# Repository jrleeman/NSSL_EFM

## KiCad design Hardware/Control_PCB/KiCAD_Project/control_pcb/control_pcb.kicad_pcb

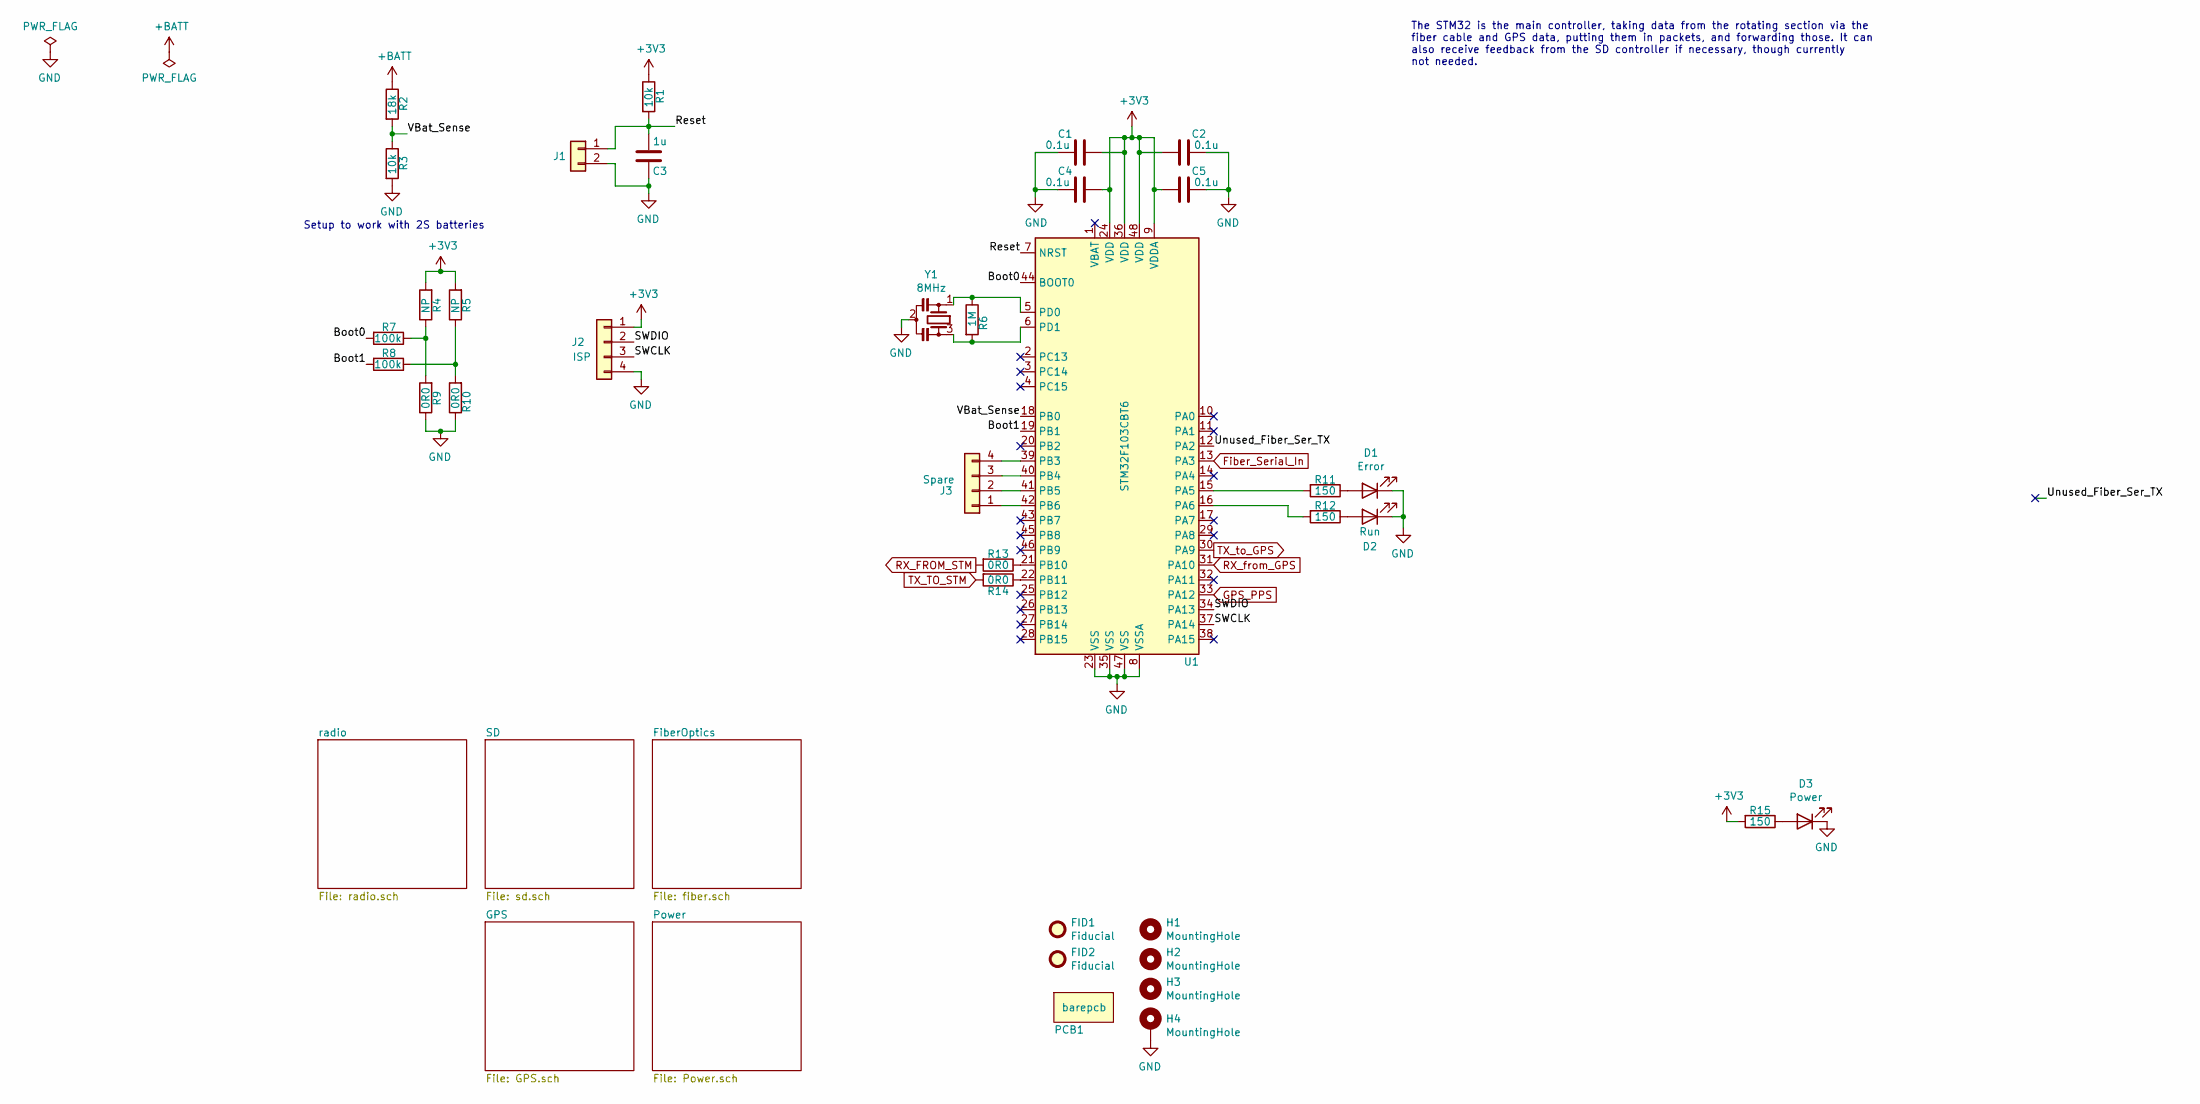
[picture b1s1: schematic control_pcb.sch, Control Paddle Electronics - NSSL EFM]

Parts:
C1, C2, C4, C5: 0.1u; C_0603_1608Metric
C3: 1u; C_0603_1608Metric
D1: Error; LED_0805_2012Metric
D2: Run; LED_0805_2012Metric
D3: Power; LED_0805_2012Metric
FID1, FID2: Fiducial; Fiducial_1mm_Mask2mm
H1, H2, H3: MountingHole; MountingHole_3.2mm_M3_ISO7380
H4: MountingHole; MountingHole_3.2mm_M3_ISO7380_Pad
J1: Conn_01x02; Pin_Header_Straight_1x02_Pitch2.54mm
J2: ISP; Pin_Header_Straight_1x04_Pitch2.54mm
J3: Spare; Pin_Header_Straight_1x04_Pitch2.54mm
PCB1: barepcb
R1, R3: 10k; R_0603_1608Metric
R2: 18k; R_0603_1608Metric
R4, R5: NP; R_0603_1608Metric
R6: 1M; R_0603_1608Metric
R7, R8: 100k; R_0603_1608Metric
R9, R10: 0R0; R_0603_1608Metric
R11, R12, R15: 150; R_0603_1608Metric
R13, R14: 1-0000006
U1: STM32F103CBT6; LQFP-48_7x7mm_Pitch0.5mm
Y1: 8MHz; Resonator

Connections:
+3V3: C1.2, C2.2, C4.2, C5.2, J2.1, R1.1, R4.2, R5.2, R15.2, U1.9 (VDDA), U1.24 (VDD), U1.36 (VDD), U1.48 (VDD); also elsewhere on the board
+BATT: R2.1; also elsewhere on the board
/Boot0: R7.2, U1.44 (BOOT0)
/Boot1: R8.2, U1.19 (PB1)
/Reset: C3.1, J1.1, R1.2, U1.7 (NRST)
/SWCLK: J2.3, U1.37 (PA14)
/SWDIO: J2.2, U1.34 (PA13)
/VBat_Sense: R2.2, R3.1, U1.18 (PB0)
Fiber_Serial_In: U1.13 (PA3); also elsewhere on the board
GND: C1.1, C2.1, C3.2, C4.1, C5.1, D1.1 (K), D2.1 (K), D3.1 (K), H4.1, J1.2, J2.4, R3.2, R9.1, R10.1, U1.8 (VSSA), U1.23 (VSS), U1.35 (VSS), U1.47 (VSS), Y1.2; also elsewhere on the board
GPS_PPS: U1.33 (PA12); also elsewhere on the board
unnamed: D1.2 (A), R11.1
unnamed: D2.2 (A), R12.1
unnamed: D3.2 (A), R15.1
unnamed: J3.1, U1.42 (PB6)
unnamed: J3.2, U1.41 (PB5)
unnamed: J3.3, U1.40 (PB4)
unnamed: J3.4, U1.39 (PB3)
unnamed: R4.1, R7.1, R9.2
unnamed: R6.1, U1.5 (PD0), Y1.1
unnamed: R6.2, U1.6 (PD1), Y1.3
unnamed: R5.1, R8.1, R10.2
unnamed: R11.2, U1.15 (PA5)
unnamed: R12.2, U1.16 (PA6)
unnamed: R13.1, U1.21 (PB10)
unnamed: R14.1, U1.22 (PB11)
RX_FROM_STM: R13.2; also elsewhere on the board
RX_from_GPS: U1.31 (PA10); also elsewhere on the board
TX_TO_STM: R14.2; also elsewhere on the board
TX_to_GPS: U1.30 (PA9); also elsewhere on the board

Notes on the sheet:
Setup to work with 2S batteries
The STM32 is the main controller, taking data from the rotating section via the fiber cable and GPS data, putting them in packets, and forwarding those. It can also receive feedback from the SD controller if necessary, though currently not needed.

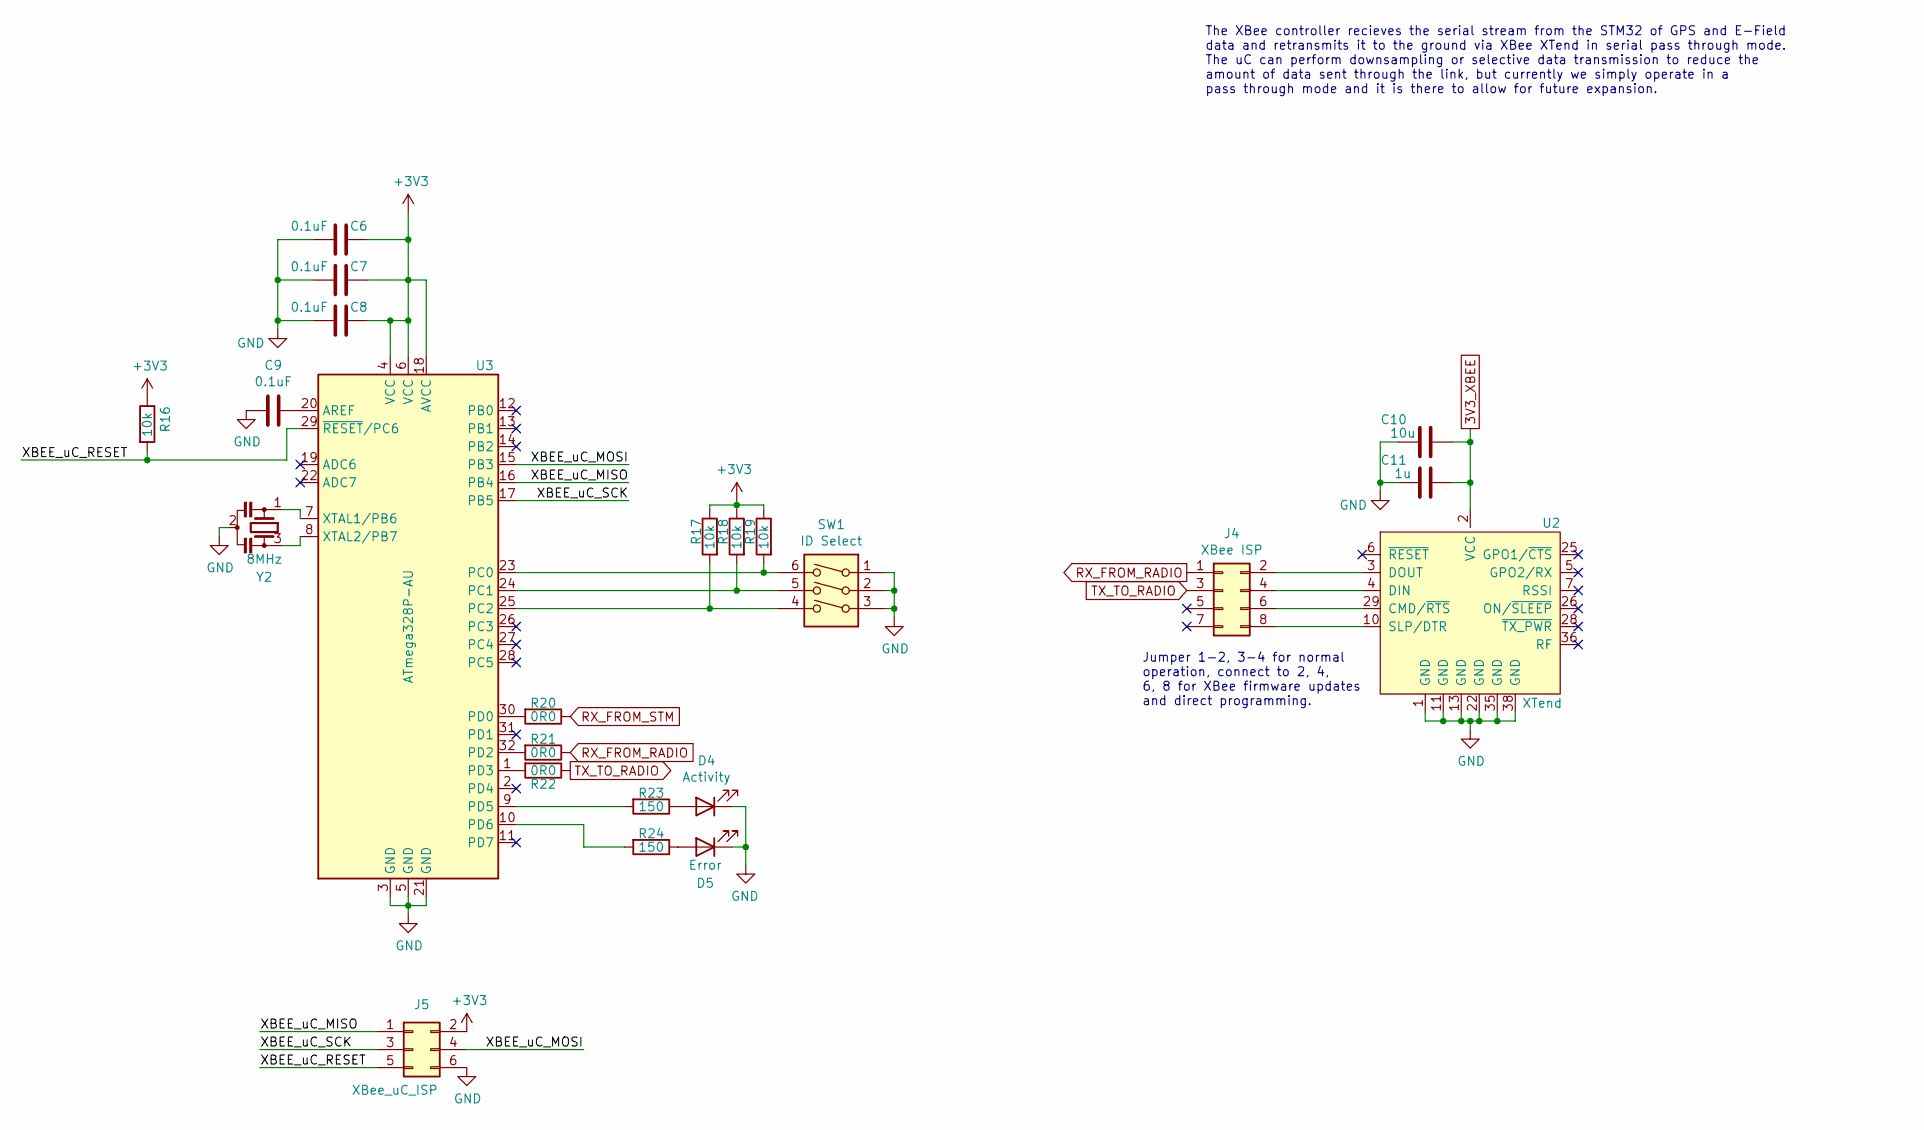
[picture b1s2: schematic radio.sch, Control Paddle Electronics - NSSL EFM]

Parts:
C6, C7, C8, C9: 1-0000007
C10: 10u; C_0603_1608Metric
C11: 1u; C_0603_1608Metric
D4: Activity; LED_D3.0mm_Horizontal_O1.27mm_Z2.0mm_Clear
D5: Error; LED_D3.0mm_Horizontal_O1.27mm_Z2.0mm_Clear
J4: XBee ISP; PinHeader_2x04_P2.54mm_Vertical
J5: XBee_uC_ISP; PinHeader_2x03_P2.54mm_Vertical
R16: 1-0000010
R17, R18, R19: 10k; R_0603_1608Metric
R20, R21, R22: 1-0000006
R23, R24: 150; R_0603_1608Metric
SW1: ID Select; KAE03TGGR
U2: XTend
U3: ATmega328P-AU; TQFP-32_7x7mm_P0.8mm
Y2: 8MHz; Resonator

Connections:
3V3_XBEE: C10.1, C11.1, U2.2 (VCC); also elsewhere on the board
+3V3: C6.1, C7.1, C8.1, J5.2, R16.1, R17.1, R18.1, R19.1, U3.4 (VCC), U3.6 (VCC), U3.18 (AVCC); also elsewhere on the board
/radio/XBEE_uC_MISO: J5.1, U3.16 (PB4)
/radio/XBEE_uC_MOSI: J5.4, U3.15 (PB3)
/radio/XBEE_uC_RESET: J5.5, R16.2, U3.29 (~RESET~/PC6)
/radio/XBEE_uC_SCK: J5.3, U3.17 (PB5)
GND: C6.2, C7.2, C8.2, C9.2, C10.2, C11.2, D4.1 (K), D5.1 (K), J5.6, SW1.1, SW1.2, SW1.3, U2.1 (GND), U2.11 (GND), U2.13 (GND), U2.22 (GND), U2.35 (GND), U2.38 (GND), U3.3 (GND), U3.5 (GND), U3.21 (GND), Y2.2; also elsewhere on the board
unnamed: C9.1, U3.20 (AREF)
unnamed: D4.2 (A), R23.1
unnamed: D5.2 (A), R24.1
unnamed: J4.2, U2.3 (DOUT)
unnamed: J4.4, U2.4 (DIN)
unnamed: J4.6, U2.29 (CMD/~RTS)
unnamed: J4.8, U2.10 (SLP/DTR)
unnamed: R17.2, SW1.4, U3.25 (PC2)
unnamed: R18.2, SW1.5, U3.24 (PC1)
unnamed: R19.2, SW1.6, U3.23 (PC0)
unnamed: R20.2, U3.30 (PD0)
unnamed: R21.2, U3.32 (PD2)
unnamed: R22.2, U3.1 (PD3)
unnamed: R23.2, U3.9 (PD5)
unnamed: R24.2, U3.10 (PD6)
unnamed: U3.7 (XTAL1/PB6), Y2.1
unnamed: U3.8 (XTAL2/PB7), Y2.3
RX_FROM_RADIO: J4.1, R21.1
RX_FROM_STM: R20.1; also elsewhere on the board
TX_TO_RADIO: J4.3, R22.1

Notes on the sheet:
The XBee controller recieves the serial stream from the STM32 of GPS and E-Field data and retransmits it to the ground via XBee XTend in serial pass through mode. The uC can perform downsampling or selective data transmission to reduce the amount of data sent through the link, but currently we simp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
Jumper 1-2, 3-4 for normal operation, connect to 2, 4, 6, 8 for XBee firmware updates and direct programming.

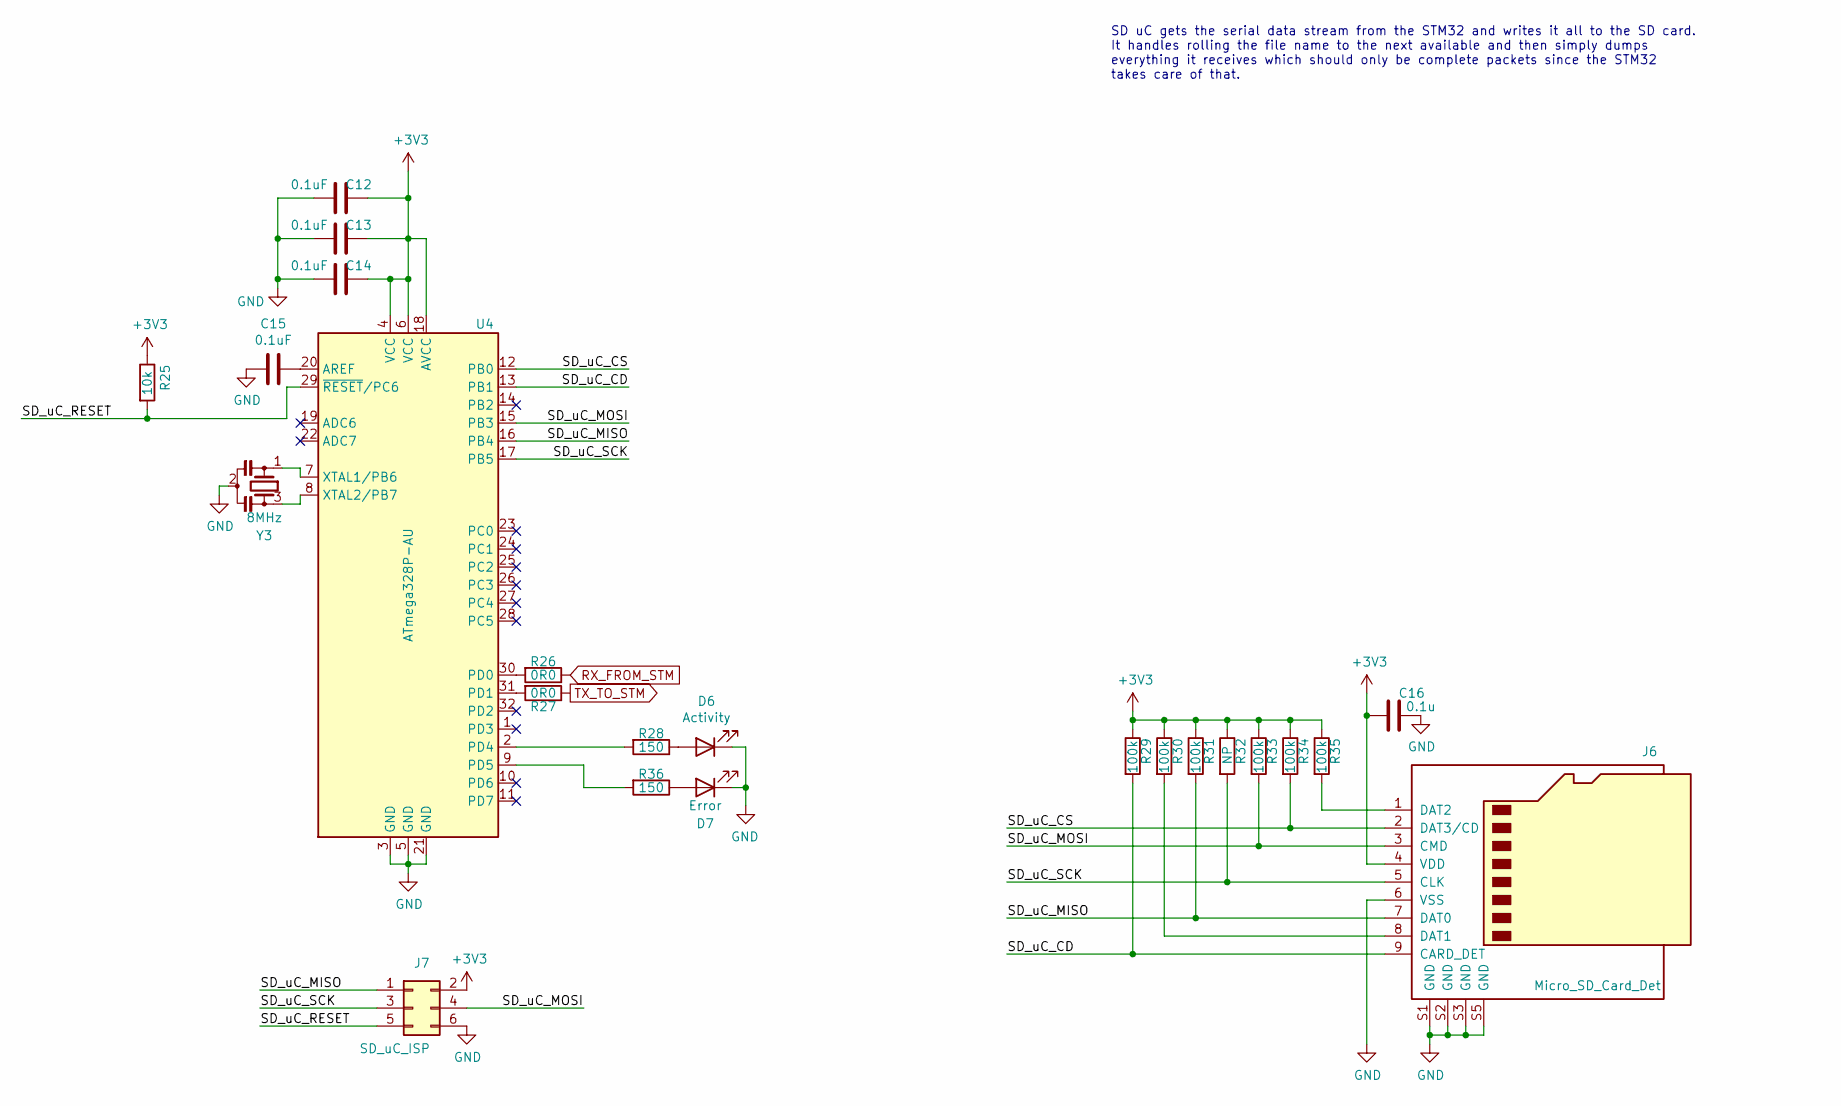
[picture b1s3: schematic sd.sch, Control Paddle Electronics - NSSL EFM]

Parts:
C12, C13, C14, C15: 1-0000007
C16: 0.1u; C_0603_1608Metric
D6: Activity; LED_D3.0mm_Horizontal_O1.27mm_Z2.0mm_Clear
D7: Error; LED_D3.0mm_Horizontal_O1.27mm_Z2.0mm_Clear
J6: Micro_SD_Card_Det; HRS_DM3CS-SF
J7: SD_uC_ISP; PinHeader_2x03_P2.54mm_Vertical
R25: 1-0000010
R26, R27: 1-0000006
R28, R36: 150; R_0603_1608Metric
R29, R30, R31, R33, R34, R35: 100k; R_0603_1608Metric
R32: NP; R_0603_1608Metric
U4: ATmega328P-AU; TQFP-32_7x7mm_P0.8mm
Y3: 8MHz; Resonator

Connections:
+3V3: C12.1, C13.1, C14.1, C16.2, J6.4 (VDD), J7.2, R25.1, R29.1, R30.1, R31.1, R32.1, R33.1, R34.1, R35.1, U4.4 (VCC), U4.6 (VCC), U4.18 (AVCC); also elsewhere on the board
/SD/SD_uC_CD: J6.9 (CARD_DET), R29.2, U4.13 (PB1)
/SD/SD_uC_CS: J6.2 (DAT3/CD), R34.2, U4.12 (PB0)
/SD/SD_uC_MISO: J6.7 (DAT0), J7.1, R31.2, U4.16 (PB4)
/SD/SD_uC_MOSI: J6.3 (CMD), J7.4, R33.2, U4.15 (PB3)
/SD/SD_uC_RESET: J7.5, R25.2, U4.29 (~RESET~/PC6)
/SD/SD_uC_SCK: J6.5 (CLK), J7.3, R32.2, U4.17 (PB5)
GND: C12.2, C13.2, C14.2, C15.2, C16.1, D6.1 (K), D7.1 (K), J6.6 (VSS), J6.S1 (GND), J6.S2 (GND), J6.S3 (GND), J6.S5 (GND), J7.6, U4.3 (GND), U4.5 (GND), U4.21 (GND), Y3.2; also elsewhere on the board
unnamed: C15.1, U4.20 (AREF)
unnamed: D6.2 (A), R28.1
unnamed: D7.2 (A), R36.1
unnamed: J6.1 (DAT2), R35.2
unnamed: J6.8 (DAT1), R30.2
unnamed: R26.2, U4.30 (PD0)
unnamed: R27.2, U4.31 (PD1)
unnamed: R28.2, U4.2 (PD4)
unnamed: R36.2, U4.9 (PD5)
unnamed: U4.7 (XTAL1/PB6), Y3.1
unnamed: U4.8 (XTAL2/PB7), Y3.3
RX_FROM_STM: R26.1; also elsewhere on the board
TX_TO_STM: R27.1; also elsewhere on the board

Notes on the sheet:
SD uC gets the serial data stream from the STM32 and writes it all to the SD card. It handles rolling the file name to the next available and then simply dumps everything it receives which should only be complete packets since the STM32 takes care of that.

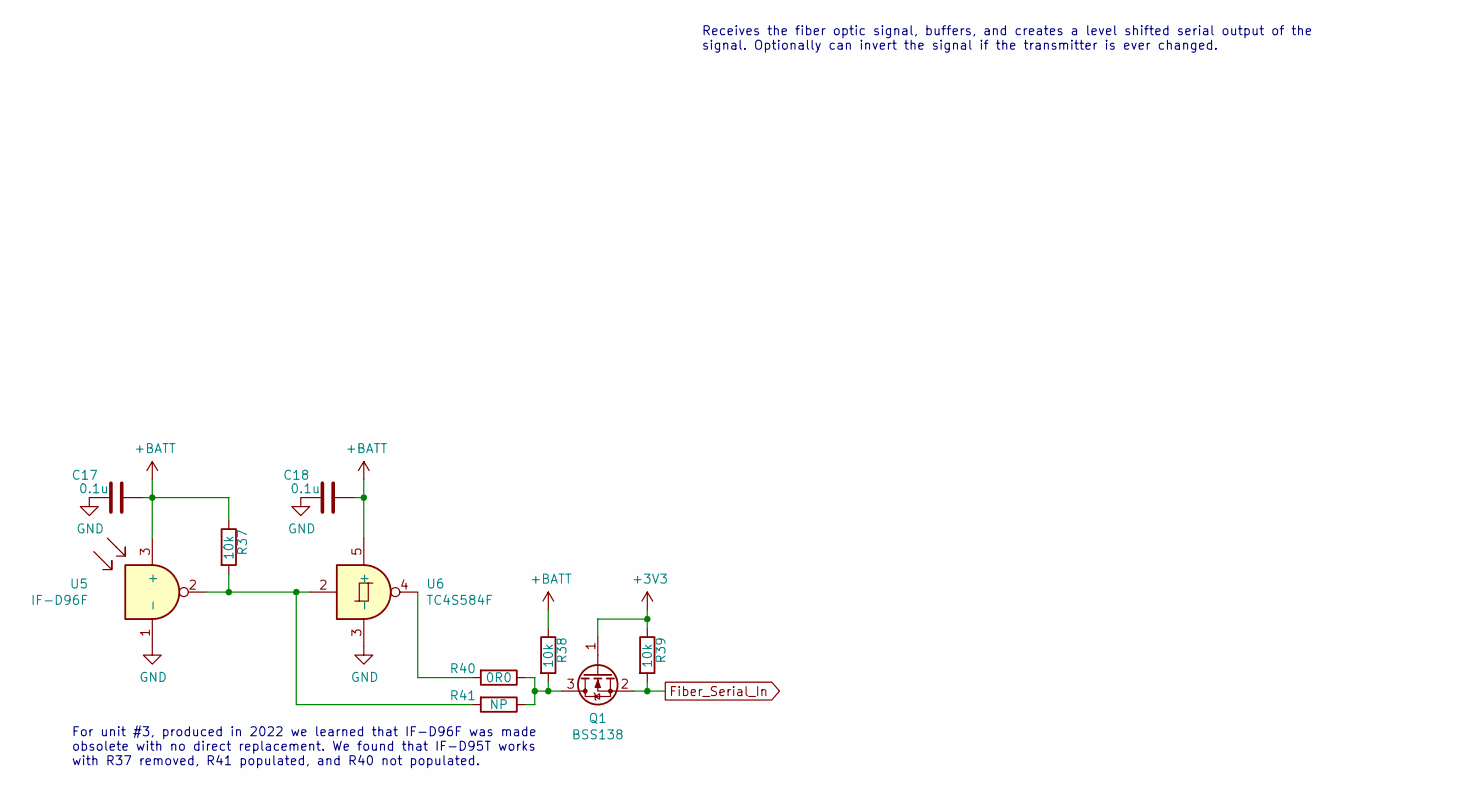
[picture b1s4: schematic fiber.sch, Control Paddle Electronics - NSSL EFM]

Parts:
C17, C18: 0.1u; C_0603_1608Metric
Q1: BSS138; SOT-23
R37, R38, R39: 10k; R_0603_1608Metric
R40: 0R0; R_0603_1608Metric
R41: NP; R_0603_1608Metric
U5: IF-D96F
U6: TC4S584F; SOT753

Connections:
+3V3: Q1.1 (G), R39.1; also elsewhere on the board
+BATT: C17.1, C18.1, R37.1, R38.1, U5.3 (+), U6.5 (+); also elsewhere on the board
Fiber_Serial_In: Q1.2 (S), R39.2; also elsewhere on the board
GND: C17.2, C18.2, U5.1 (-), U6.3 (-); also elsewhere on the board
unnamed: Q1.3 (D), R38.2, R40.1, R41.1
unnamed: R37.2, R41.2, U5.2, U6.2
unnamed: R40.2, U6.4

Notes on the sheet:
Receives the fiber optic signal, buffers, and creates a level shifted serial output of the signal. Optionally can invert the signal if the transmitter is ever changed.
For unit #3, produced in 2022 we learned that IF-D96F was made obsolete with no direct replacement. We found that IF-D95T works with R37 removed, R41 populated, and R40 not populated.

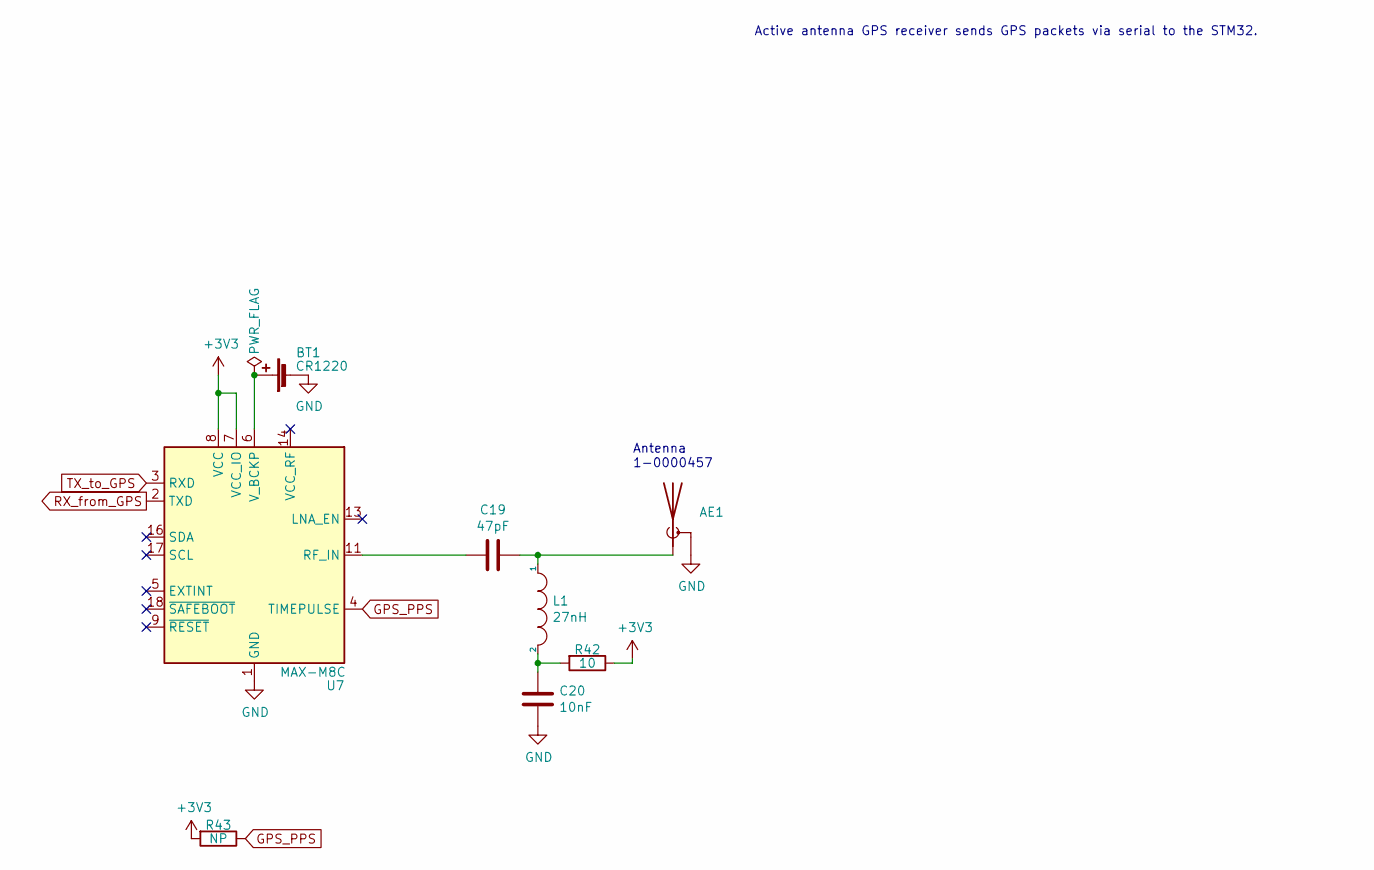
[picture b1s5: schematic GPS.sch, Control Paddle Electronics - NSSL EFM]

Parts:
AE1: Antenna_Shield; SMA
BT1: CR1220; S8411-45R
C19: 47pF; C_0603_1608Metric
C20: 10nF; C_0603_1608Metric
L1: 27nH; R_0603_HandSoldering
R42: 10; R_0603_1608Metric
R43: NP; R_0603_1608Metric
U7: MAX-M8C; XCVR_MAX-M8C-0-10

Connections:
+3V3: R42.1, R43.2, U7.7 (VCC_IO), U7.8 (VCC); also elsewhere on the board
GND: AE1.2 (Shield), BT1.2 (-), C20.1, U7.1 (GND), U7.10 (GND), U7.12 (GND); also elsewhere on the board
GPS_PPS: R43.1, U7.4 (TIMEPULSE); also elsewhere on the board
unnamed: AE1.1 (A), C19.1, L1.1
unnamed: BT1.1 (+), U7.6 (V_BCKP)
unnamed: C19.2, U7.11 (RF_IN)
unnamed: C20.2, L1.2, R42.2
RX_from_GPS: U7.2 (TXD); also elsewhere on the board
TX_to_GPS: U7.3 (RXD); also elsewhere on the board

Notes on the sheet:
Antenna 1-0000457
Active antenna GPS receiver sends GPS packets via serial to the STM32.

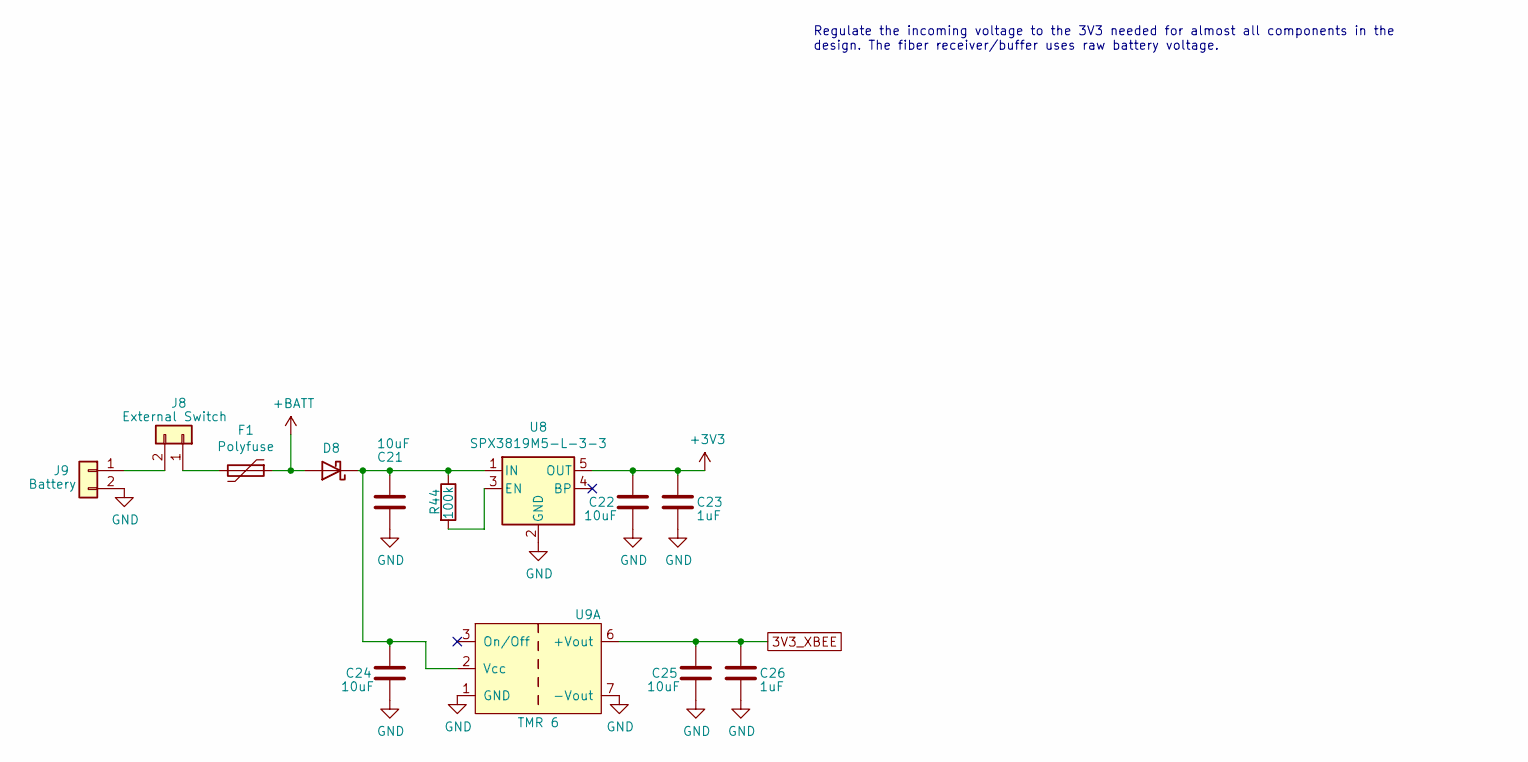
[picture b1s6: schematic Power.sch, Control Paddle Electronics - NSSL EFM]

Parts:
C21, C22, C24, C25: 1-0000075
C23, C26: 1-0000018
D8: D_Schottky; D_SOD-123F
F1: Polyfuse; RGEF250
J8: External Switch; PinHeader_1x02_P2.54mm_Vertical
J9: Battery; PinHeader_1x02_P2.54mm_Vertical
R44: 1-0000174
U8: SPX3819M5-L-3-3; SOT-23-5
U9: 1-0000946

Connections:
3V3_XBEE: C25.1, C26.1, U9.6 (+Vout); also elsewhere on the board
+3V3: C22.1, C23.1, U8.5 (OUT); also elsewhere on the board
+BATT: D8.2 (A), F1.1; also elsewhere on the board
GND: C21.2, C22.2, C23.2, C24.2, C25.2, C26.2, J9.2, U8.2 (GND), U9.1 (GND), U9.7 (-Vout); also elsewhere on the board
unnamed: C21.1, C24.1, D8.1 (K), R44.1, U8.1 (IN), U9.2 (Vcc)
unnamed: F1.2, J8.1
unnamed: J8.2, J9.1
unnamed: R44.2, U8.3 (EN)

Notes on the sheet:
Regulate the incoming voltage to the 3V3 needed for almost all components in the design. The fiber receiver/buffer uses raw battery voltage.

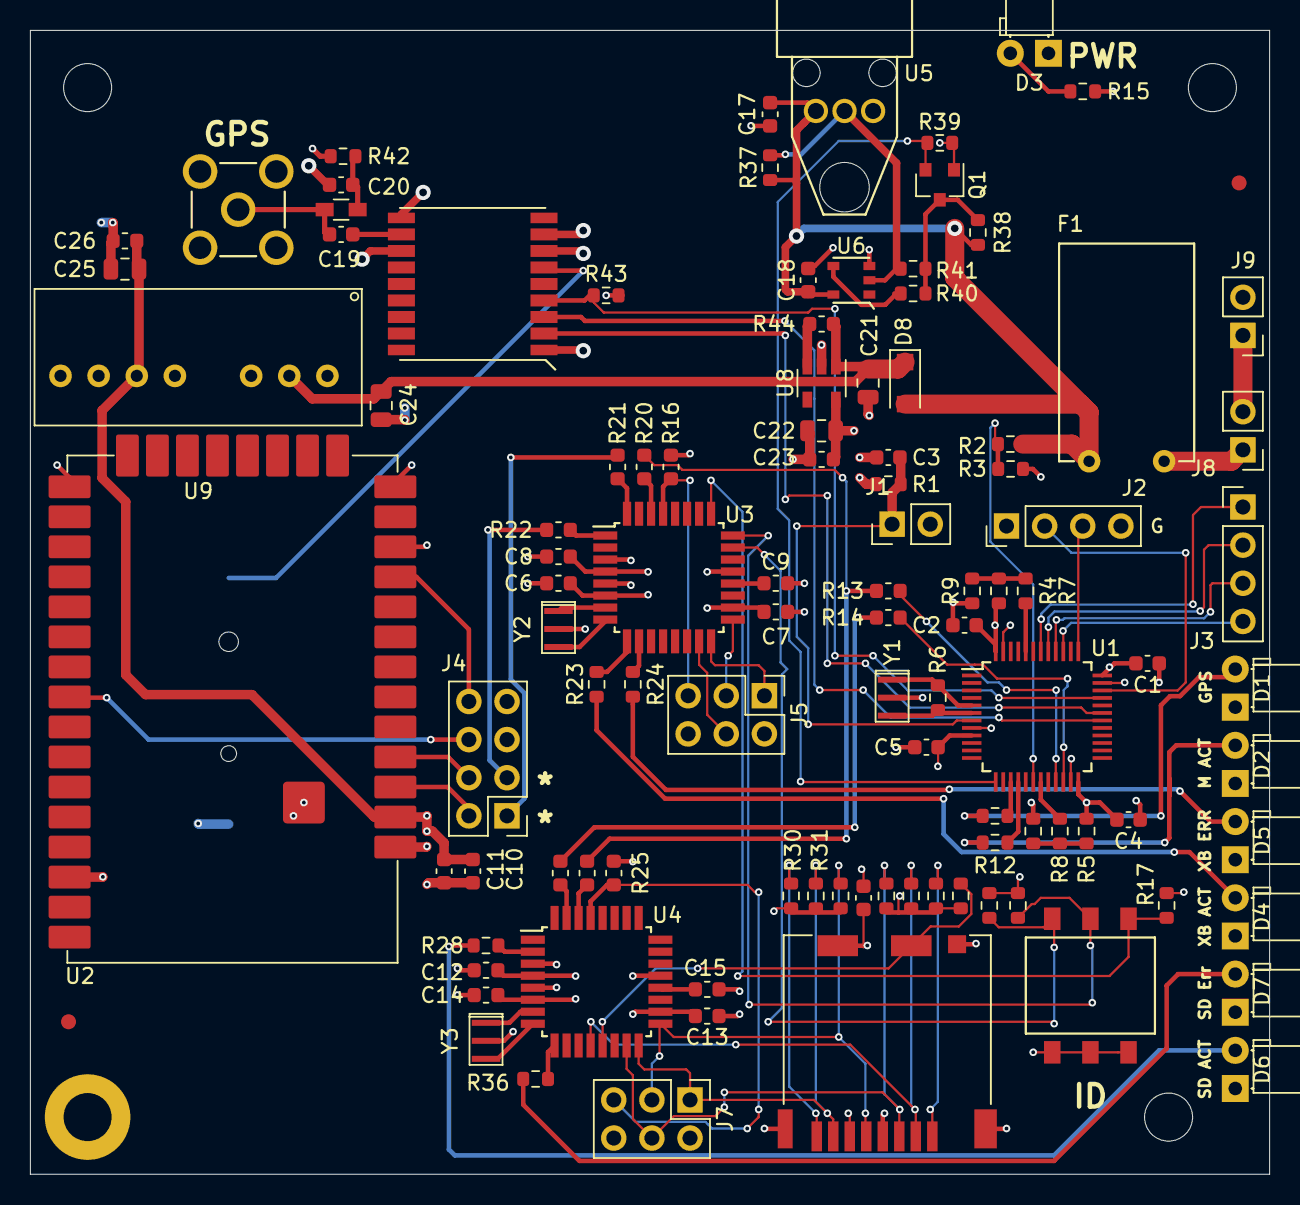
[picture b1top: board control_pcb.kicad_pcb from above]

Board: 4 copper layers, 82.6 x 76.2 mm, 112 parts (1 on the bottom side), 82 nets.

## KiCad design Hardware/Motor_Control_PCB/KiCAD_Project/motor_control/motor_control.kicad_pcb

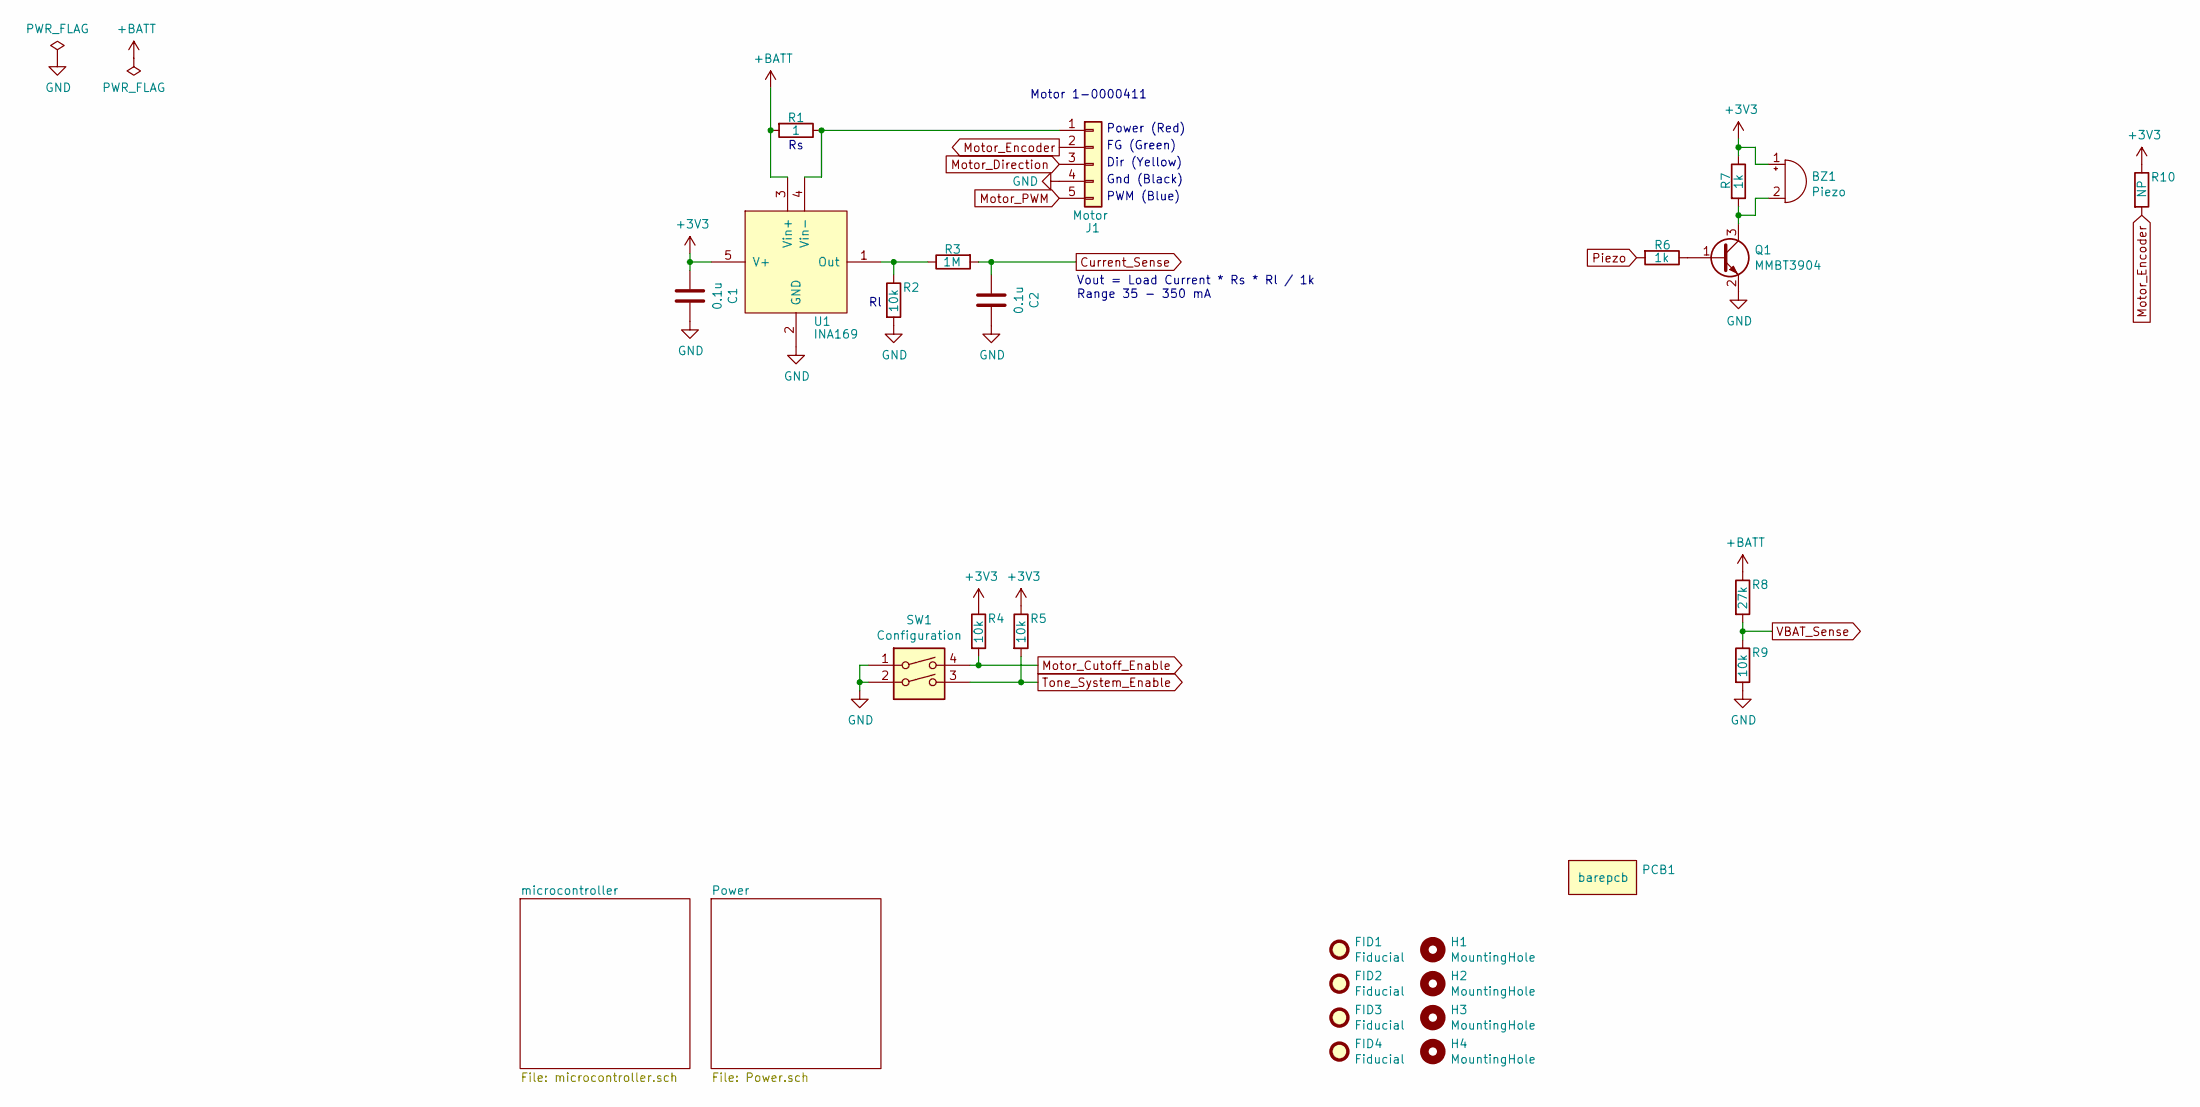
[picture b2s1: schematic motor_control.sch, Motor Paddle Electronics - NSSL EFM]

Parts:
BZ1: Piezo; PS1240P02BT
C1, C2: 0.1u; C_0603_HandSoldering
FID1, FID2, FID3, FID4: Fiducial; Fiducial_1mm_Dia_2.54mm_Outer_CopperTop
H1, H2, H3, H4: MountingHole; MountingHole_3.2mm_M3_ISO7380
J1: Motor; Pin_Header_Straight_1x05_Pitch2.54mm
PCB1: barepcb
Q1: MMBT3904; SOT-23
R1: 1; R_Axial_DIN0614_L14.3mm_D5.7mm_P20.32mm_Horizontal
R2, R4, R5, R9: 10k; R_0603_HandSoldering
R3: 1M; R_0603_HandSoldering
R6, R7: 1k; R_0603_HandSoldering
R8: 27k; R_0603_HandSoldering
R10: NP; R_0603_HandSoldering
SW1: Configuration; KAE02LGGR
U1: INA169; SOT-23-5_HandSoldering

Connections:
+3V3: BZ1.1 (-), C1.2, R4.1, R5.1, R7.1, R10.1, U1.5 (V+); also elsewhere on the board
+BATT: R1.2, R8.1, U1.3 (Vin+); also elsewhere on the board
Current_Sense: C2.2, R3.2; also elsewhere on the board
GND: C1.1, C2.1, J1.4, Q1.2 (E), R2.2, R9.2, SW1.1, SW1.2, U1.2 (GND); also elsewhere on the board
Motor_Cutoff_Enable: R4.2, SW1.4; also elsewhere on the board
Motor_Direction: J1.3; also elsewhere on the board
Motor_Encoder: J1.2, R10.2; also elsewhere on the board
Motor_PWM: J1.5; also elsewhere on the board
unnamed: BZ1.2 (+), Q1.3 (C), R7.2
unnamed: J1.1, R1.1, U1.4 (Vin-)
unnamed: Q1.1 (B), R6.1
unnamed: R2.1, R3.1, U1.1 (Out)
Piezo: R6.2; also elsewhere on the board
Tone_System_Enable: R5.2, SW1.3; also elsewhere on the board
VBAT_Sense: R8.2, R9.1; also elsewhere on the board

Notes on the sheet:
Vout = Load Current * Rs * Rl / 1k Range 35 - 350 mA
Motor 1-0000411
PWM (Blue)
Gnd (Black)
Dir (Yellow)
FG (Green)
Power (Red)

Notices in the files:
parts and their libraries:
Copyright 2016 Accelerated Designs. All rights reserved.
